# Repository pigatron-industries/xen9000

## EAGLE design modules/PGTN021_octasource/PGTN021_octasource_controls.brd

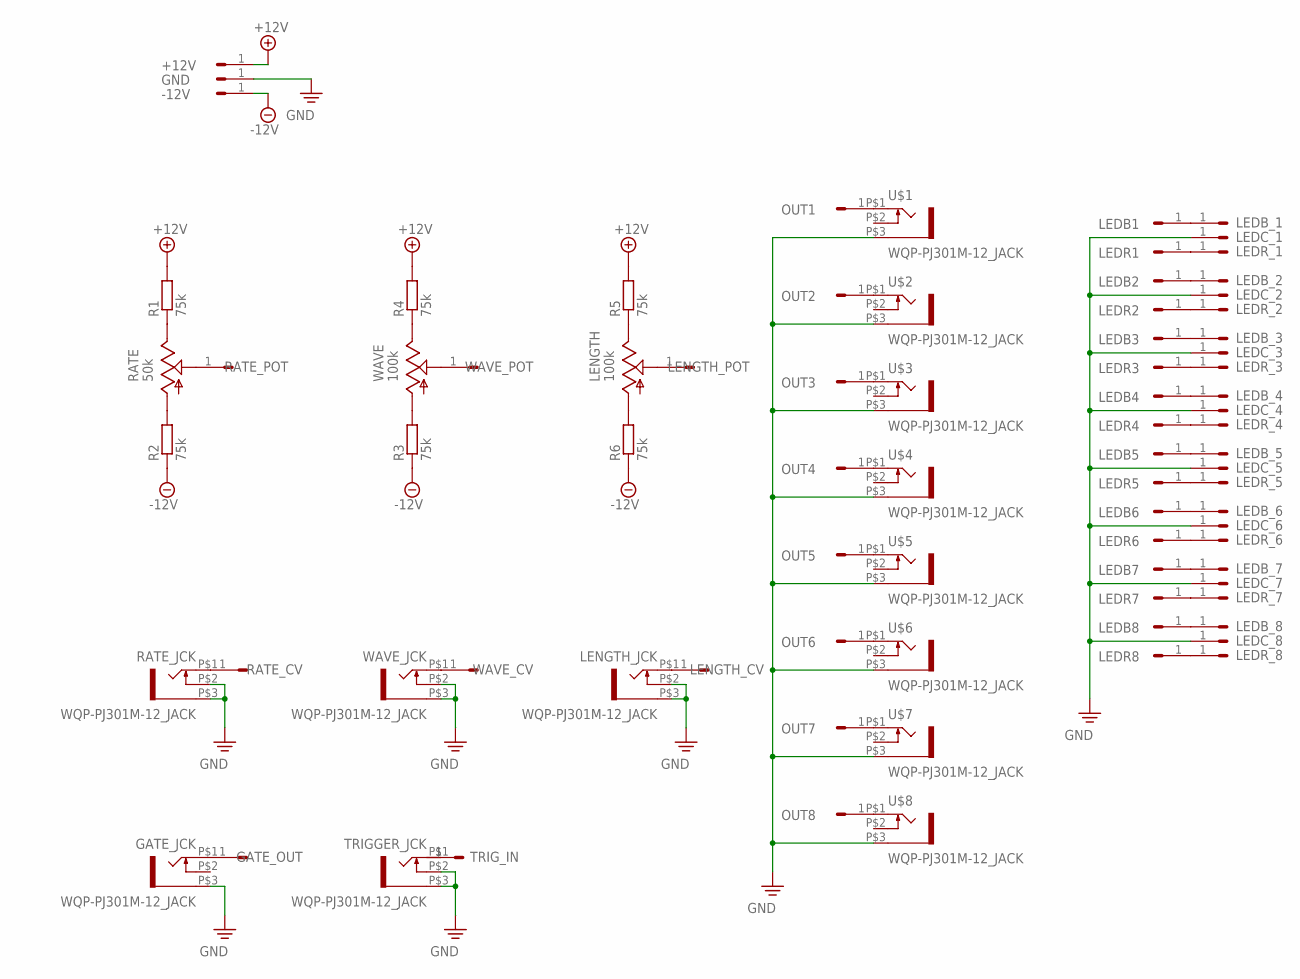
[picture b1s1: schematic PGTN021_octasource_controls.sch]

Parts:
+12V: HEADER/MALE/01
-12V: HEADER/MALE/01
GATE_JCK: WQP-PJ301M-12_JACK
GATE_OUT: HEADER/MALE/01
GND: HEADER/MALE/01
LEDB1, LEDB2, LEDB3, LEDB4, LEDB5, LEDB6, LEDB7, LEDB8: HEADER/MALE/01
LEDB_1, LEDB_2, LEDB_3, LEDB_4, LEDB_5, LEDB_6, LEDB_7, LEDB_8: HEADER/MALE/01
LEDC_1, LEDC_2, LEDC_3, LEDC_4, LEDC_5, LEDC_6, LEDC_7, LEDC_8: HEADER/MALE/01
LEDR1, LEDR2, LEDR3, LEDR4, LEDR5, LEDR6, LEDR7, LEDR8: HEADER/MALE/01
LEDR_1, LEDR_2, LEDR_3, LEDR_4, LEDR_5, LEDR_6, LEDR_7, LEDR_8: HEADER/MALE/01
LENGTH: 100k; 9MM_SNAP-IN_POT
LENGTH_CV: HEADER/MALE/01
LENGTH_JCK: WQP-PJ301M-12_JACK
LENGTH_POT: HEADER/MALE/01
OUT1, OUT2, OUT3, OUT4, OUT5, OUT6, OUT7, OUT8: HEADER/MALE/01
R1, R2, R3, R4, R5, R6: 75k; RESISTOR/7.5
RATE: 50k; 9MM_SNAP-IN_POT
RATE_CV: HEADER/MALE/01
RATE_JCK: WQP-PJ301M-12_JACK
RATE_POT: HEADER/MALE/01
TRIGGER_JCK: WQP-PJ301M-12_JACK
TRIG_IN: HEADER/MALE/01
U$1, U$2, U$3, U$4, U$5, U$6, U$7, U$8: WQP-PJ301M-12_JACK
WAVE: 100k; 9MM_SNAP-IN_POT
WAVE_CV: HEADER/MALE/01
WAVE_JCK: WQP-PJ301M-12_JACK
WAVE_POT: HEADER/MALE/01

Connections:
+12V: +12V.1, R1.2, R4.2, R5.2
-12V: -12V.1, R2.1, R3.1, R6.1
unnamed: R2.2, RATE.1 (A)
unnamed: R1.1, RATE.3 (E)
unnamed: RATE_CV.1, RATE_JCK.P$1 (2)
unnamed: RATE.2 (S), RATE_POT.1
unnamed: R3.2, WAVE.1 (A)
unnamed: R4.1, WAVE.3 (E)
unnamed: WAVE.2 (S), WAVE_POT.1
unnamed: LENGTH.3 (E), R5.1
unnamed: LENGTH.1 (A), R6.2
unnamed: LENGTH.2 (S), LENGTH_POT.1
unnamed: LENGTH_CV.1, LENGTH_JCK.P$1 (2)
unnamed: WAVE_CV.1, WAVE_JCK.P$1 (2)
unnamed: GATE_JCK.P$1 (2), GATE_OUT.1
unnamed: OUT1.1, U$1.P$1 (2)
unnamed: OUT2.1, U$2.P$1 (2)
unnamed: OUT3.1, U$3.P$1 (2)
unnamed: OUT4.1, U$4.P$1 (2)
unnamed: OUT5.1, U$5.P$1 (2)
unnamed: OUT6.1, U$6.P$1 (2)
unnamed: OUT7.1, U$7.P$1 (2)
unnamed: OUT8.1, U$8.P$1 (2)
unnamed: LEDB1.1, LEDB_1.1
unnamed: LEDB2.1, LEDB_2.1
unnamed: LEDB3.1, LEDB_3.1
unnamed: LEDB4.1, LEDB_4.1
unnamed: LEDB5.1, LEDB_5.1
unnamed: LEDB6.1, LEDB_6.1
unnamed: LEDB7.1, LEDB_7.1
unnamed: LEDB8.1, LEDB_8.1
unnamed: LEDR1.1, LEDR_1.1
unnamed: LEDR2.1, LEDR_2.1
unnamed: LEDR3.1, LEDR_3.1
unnamed: LEDR4.1, LEDR_4.1
unnamed: LEDR5.1, LEDR_5.1
unnamed: LEDR6.1, LEDR_6.1
unnamed: LEDR7.1, LEDR_7.1
unnamed: LEDR8.1, LEDR_8.1
unnamed: TRIGGER_JCK.P$1 (2), TRIG_IN.1
PE: GATE_JCK.P$3 (1), GND.1, LEDC_1.1, LEDC_2.1, LEDC_3.1, LEDC_4.1, LEDC_5.1, LEDC_6.1, LEDC_7.1, LEDC_8.1, LENGTH_JCK.P$2 (3), LENGTH_JCK.P$3 (1), RATE_JCK.P$2 (3), RATE_JCK.P$3 (1), TRIGGER_JCK.P$2 (3), TRIGGER_JCK.P$3 (1), U$1.P$3 (1), U$2.P$3 (1), U$3.P$3 (1), U$4.P$3 (1), U$5.P$3 (1), U$6.P$3 (1), U$7.P$3 (1), U$8.P$3 (1), WAVE_JCK.P$2 (3), WAVE_JCK.P$3 (1)

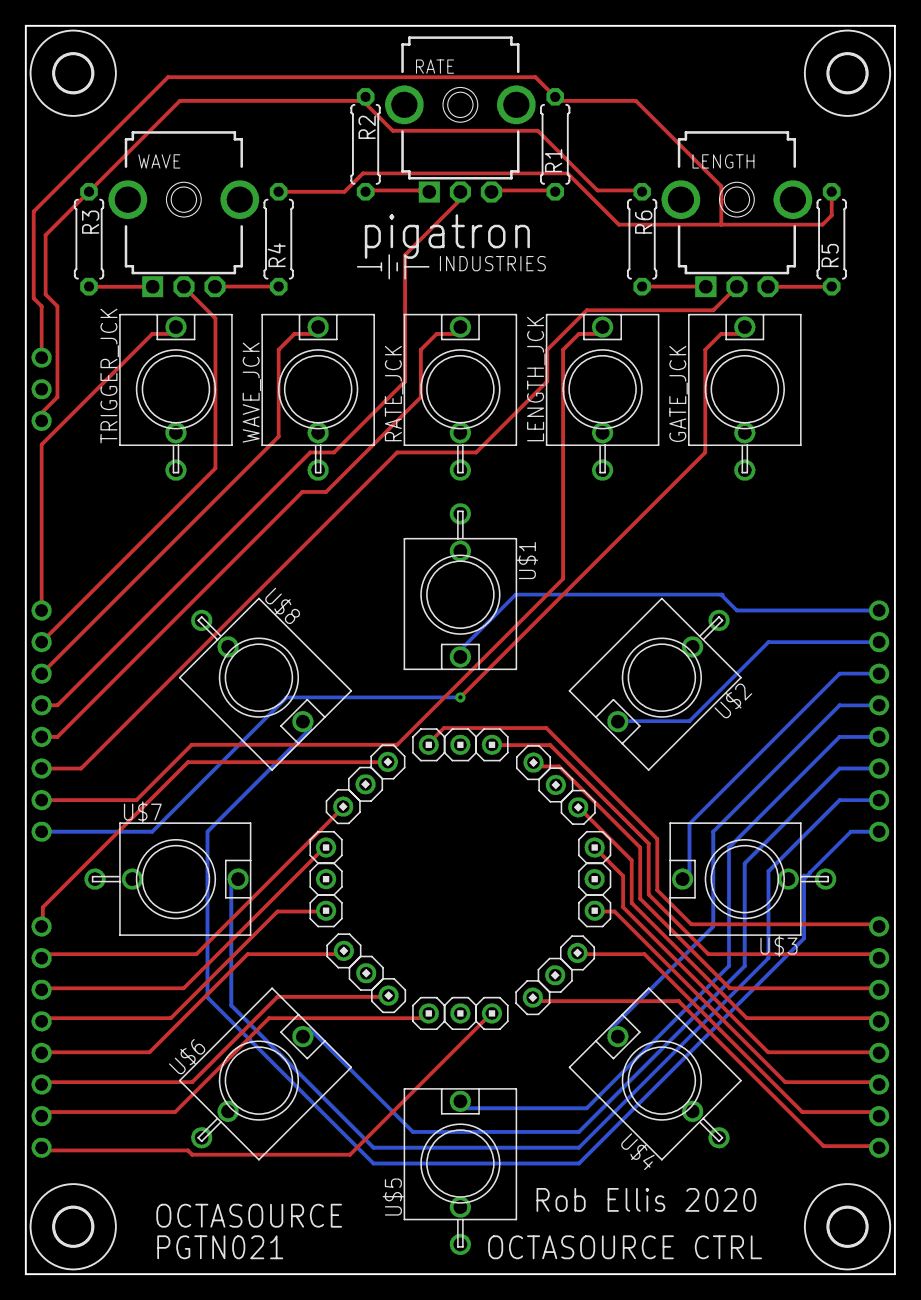
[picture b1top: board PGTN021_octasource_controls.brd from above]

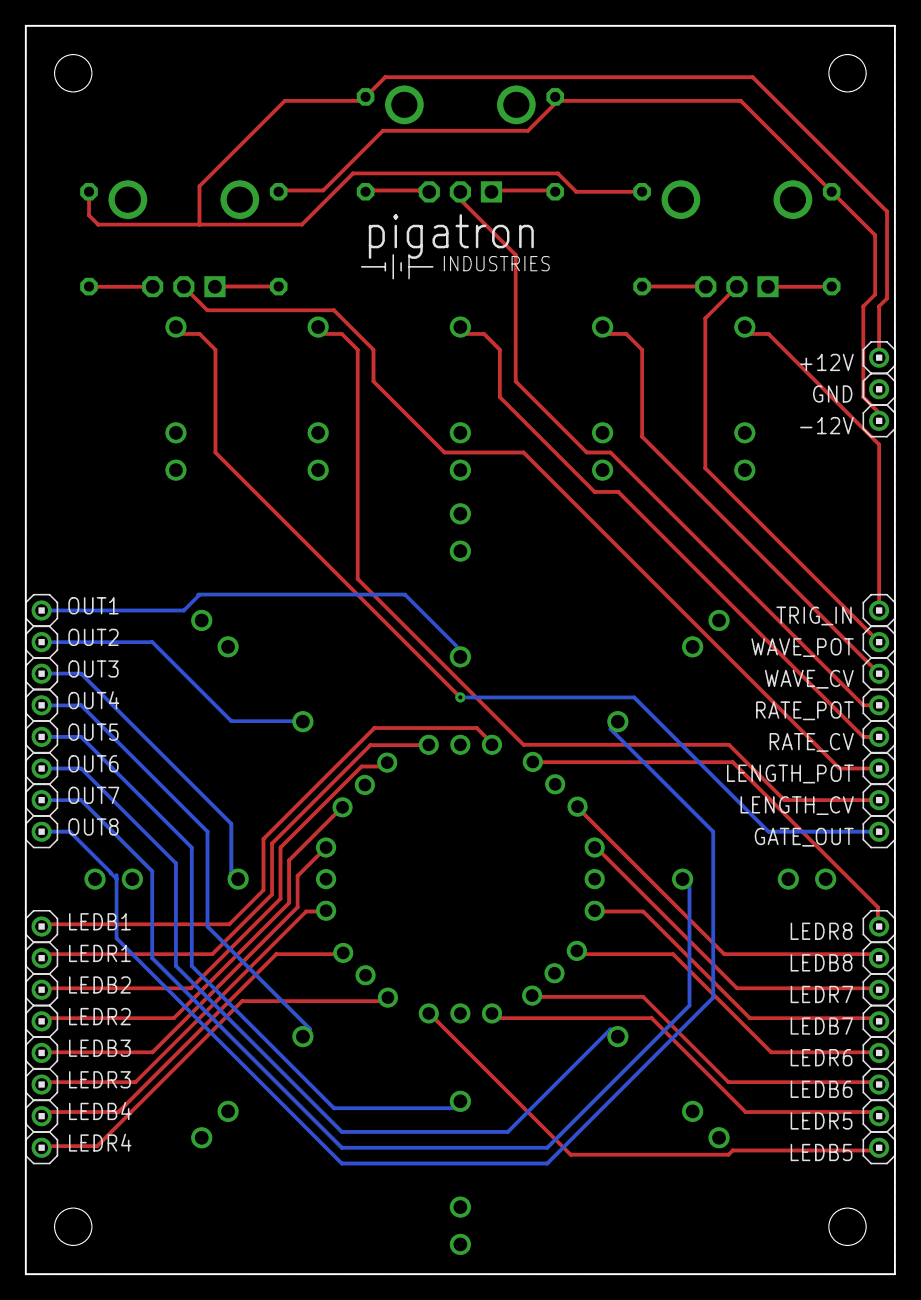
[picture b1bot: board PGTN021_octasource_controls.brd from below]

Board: 2 copper layers, 69.8 x 100.3 mm, 87 parts (36 on the bottom side), 41 nets.

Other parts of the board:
U$9, U$10, U$11, U$12: STANDOFF/3.0
U$13, U$14: PIGATRON-LOGO

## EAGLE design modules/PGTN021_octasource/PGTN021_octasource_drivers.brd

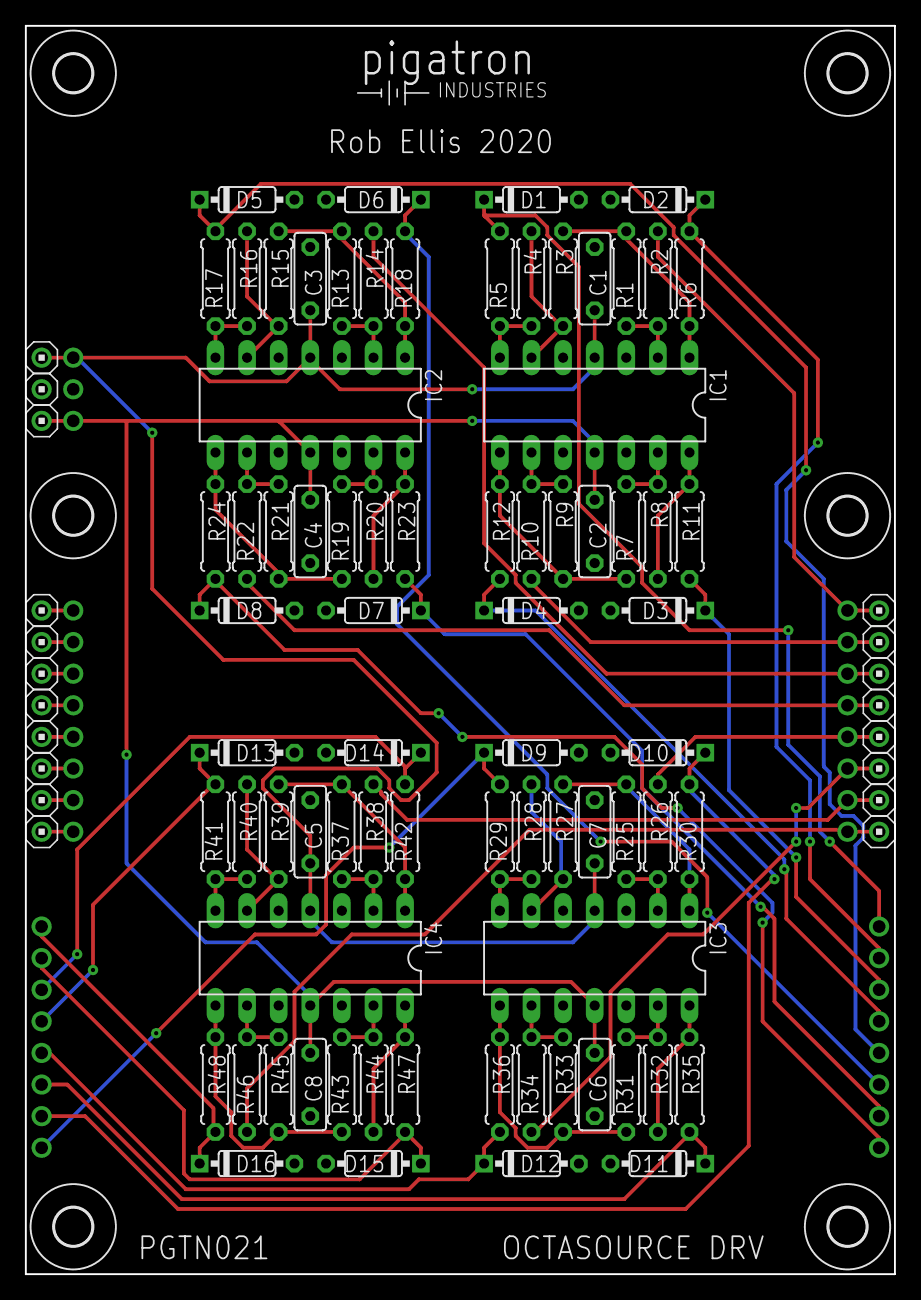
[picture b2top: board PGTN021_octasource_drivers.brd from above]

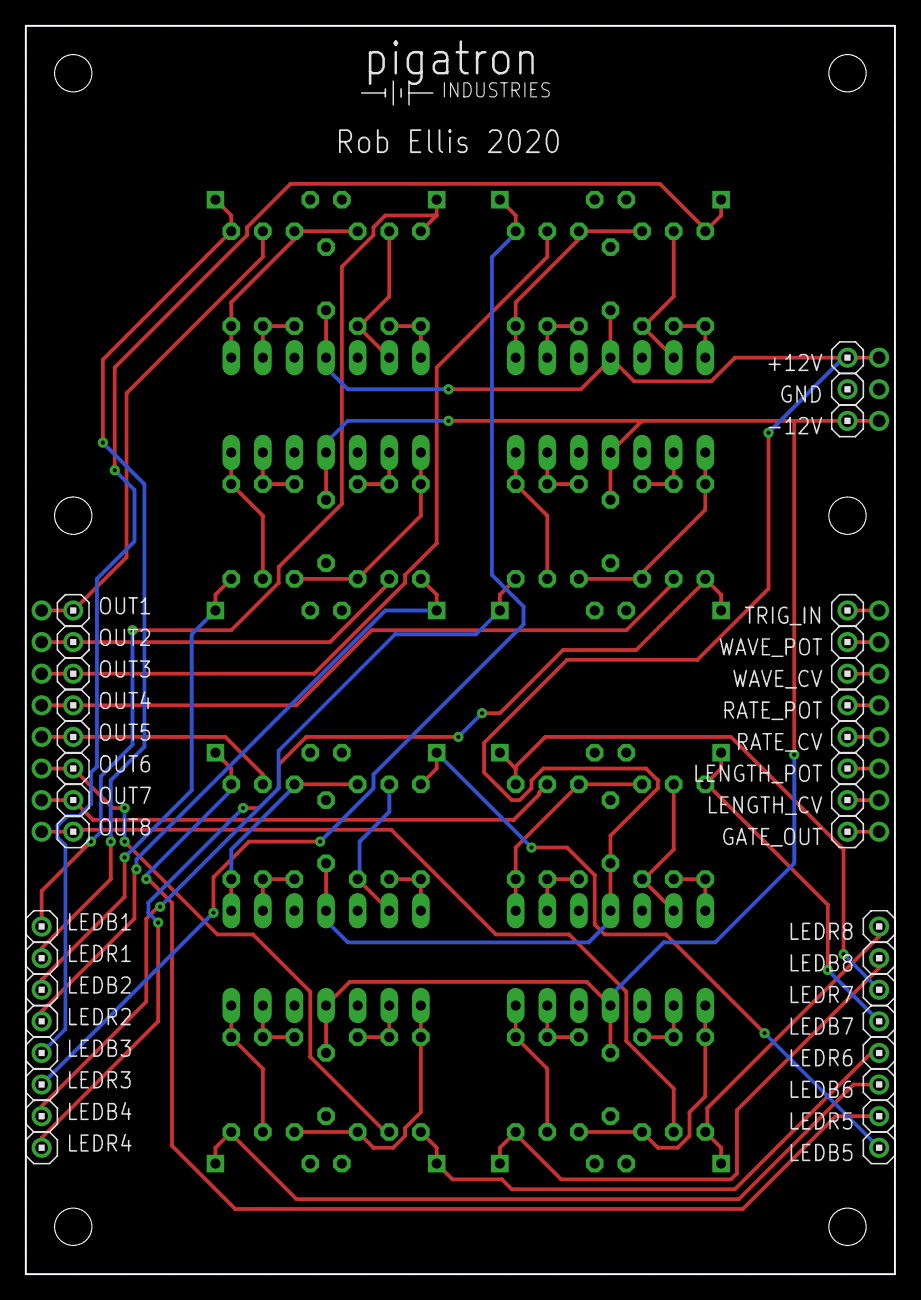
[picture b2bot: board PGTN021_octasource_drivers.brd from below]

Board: 2 copper layers, 69.8 x 100.3 mm, 138 parts (36 on the bottom side), 67 nets.

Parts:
+12V, +12V1: HEADER/MALE/01
-12V, -12V1: HEADER/MALE/01
C1, C2, C3, C4, C5, C6, C7, C8: CERAMICDISC/5
D1, D2, D3, D4, D5, D6, D7, D8, D9, D10, D11, D12, D13, D14, D15, D16: DO35-7
GATE_OUT, GATE_OUT1: HEADER/MALE/01
GND, GND1: HEADER/MALE/01
IC1, IC2, IC3, IC4: TL084P; DIL14
LEDB1, LEDB2, LEDB3, LEDB4, LEDB5, LEDB6, LEDB7, LEDB8: HEADER/MALE/01
LEDR1, LEDR2, LEDR3, LEDR4, LEDR5, LEDR6, LEDR7, LEDR8: HEADER/MALE/01
LENGTH_CV, LENGTH_CV1: HEADER/MALE/01
LENGTH_POT, LENGTH_POT1: HEADER/MALE/01
OUT1, OUT2, OUT3, OUT4, OUT5, OUT6, OUT7, OUT8, OUT9, OUT10, OUT11, OUT12, OUT13, OUT14, OUT15, OUT16: HEADER/MALE/01
R1, R9, R13, R21, R25, R33, R37, R45: 100k; RESISTOR/7.5
R2, R3, R4, R7, R8, R10, R14, R15, R16, R19, R20, R22, R26, R27, R28, R31, R32, R34, R38, R39, R40, R43, R44, R46: 10k; RESISTOR/7.5
R5, R11, R17, R23, R29, R35, R41, R47: 2.7k; RESISTOR/7.5
R6, R12, R18, R24, R30, R36, R42, R48: 4.7k; RESISTOR/7.5
RATE_CV, RATE_CV1: HEADER/MALE/01
RATE_POT, RATE_POT1: HEADER/MALE/01
TRIG_IN, TRIG_IN1: HEADER/MALE/01
U$1, U$2: PIGATRON-LOGO
U$4, U$5, U$9, U$10, U$11, U$12: STANDOFF/3.0
WAVE_CV, WAVE_CV1: HEADER/MALE/01
WAVE_POT, WAVE_POT1: HEADER/MALE/01

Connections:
+12V: +12V.1, +12V1.1, C1.1, C3.1, C5.1, C7.1, IC1.4, IC2.4, IC3.4, IC4.4
-12V: -12V.1, -12V1.1, C2.2, C4.2, C6.2, C8.2, IC1.11, IC2.11, IC3.11, IC4.11
unnamed: IC1.6, R3.2, R4.1
unnamed: IC1.2, R1.1, R2.2
unnamed: IC1.1, R1.2, R3.1, R6.1
unnamed: OUT1.1, OUT9.1, R2.1
unnamed: IC1.7, R4.2, R5.1
unnamed: D1.C, LEDB1.1, R5.2
unnamed: D2.C, LEDR1.1, R6.2
unnamed: IC1.13, R7.2, R8.1
unnamed: IC1.9, R9.1, R10.2
unnamed: OUT2.1, OUT10.1, R10.1
unnamed: IC1.14, R8.2, R11.1
unnamed: IC1.8, R7.1, R9.2, R12.1
unnamed: IC2.2, R13.1, R14.2
unnamed: D3.C, LEDB2.1, R11.2
unnamed: D4.C, LEDR2.1, R12.2
unnamed: IC2.1, R13.2, R15.1, R18.1
unnamed: IC2.6, R15.2, R16.1
unnamed: OUT3.1, OUT11.1, R14.1
unnamed: IC2.7, R16.2, R17.1
unnamed: D5.C, LEDB3.1, R17.2
unnamed: D6.C, LEDR3.1, R18.2
unnamed: IC2.13, R19.2, R20.1
unnamed: IC2.9, R21.1, R22.2
unnamed: IC2.14, R20.2, R23.1
unnamed: IC2.8, R19.1, R21.2, R24.1
unnamed: D7.C, LEDB4.1, R23.2
unnamed: D8.C, LEDR4.1, R24.2
unnamed: OUT4.1, OUT12.1, R22.1
unnamed: IC3.2, R25.1, R26.2
unnamed: IC3.1, R25.2, R27.1, R30.1
unnamed: IC3.6, R27.2, R28.1
unnamed: OUT5.1, OUT13.1, R26.1
unnamed: IC3.7, R28.2, R29.1
unnamed: D9.C, LEDB5.1, R29.2
unnamed: D10.C, LEDR5.1, R30.2
unnamed: IC3.13, R31.2, R32.1
unnamed: IC3.9, R33.1, R34.2
unnamed: IC3.14, R32.2, R35.1
unnamed: IC3.8, R31.1, R33.2, R36.1
unnamed: D11.C, LEDB6.1, R35.2
unnamed: D12.C, LEDR6.1, R36.2
unnamed: OUT6.1, OUT14.1, R34.1
unnamed: RATE_POT.1, RATE_POT1.1
unnamed: IC4.2, R37.1, R38.2
unnamed: IC4.1, R37.2, R39.1, R42.1
unnamed: IC4.6, R39.2, R40.1
unnamed: OUT7.1, OUT15.1, R38.1
unnamed: IC4.7, R40.2, R41.1
unnamed: D13.C, LEDB7.1, R41.2
unnamed: D14.C, LEDR7.1, R42.2
unnamed: IC4.13, R43.2, R44.1
unnamed: IC4.9, R45.1, R46.2
unnamed: IC4.14, R44.2, R47.1
unnamed: IC4.8, R43.1, R45.2, R48.1
unnamed: D15.C, LEDB8.1, R47.2
unnamed: D16.C, LEDR8.1, R48.2
unnamed: OUT8.1, OUT16.1, R46.1
unnamed: RATE_CV.1, RATE_CV1.1
unnamed: GATE_OUT.1, GATE_OUT1.1
unnamed: TRIG_IN.1, TRIG_IN1.1
unnamed: WAVE_CV.1, WAVE_CV1.1
unnamed: LENGTH_CV.1, LENGTH_CV1.1
unnamed: LENGTH_POT.1, LENGTH_POT1.1
unnamed: WAVE_POT.1, WAVE_POT1.1
PE: C1.2, C2.1, C3.2, C4.1, C5.2, C6.1, C7.2, C8.1, D1.A, D2.A, D3.A, D4.A, D5.A, D6.A, D7.A, D8.A, D9.A, D10.A, D11.A, D12.A, D13.A, D14.A, D15.A, D16.A, GND.1, GND1.1, IC1.3, IC1.5, IC1.10, IC1.12, IC2.3, IC2.5, IC2.10, IC2.12, IC3.3, IC3.5, IC3.10, IC3.12, IC4.3, IC4.5, IC4.10, IC4.12

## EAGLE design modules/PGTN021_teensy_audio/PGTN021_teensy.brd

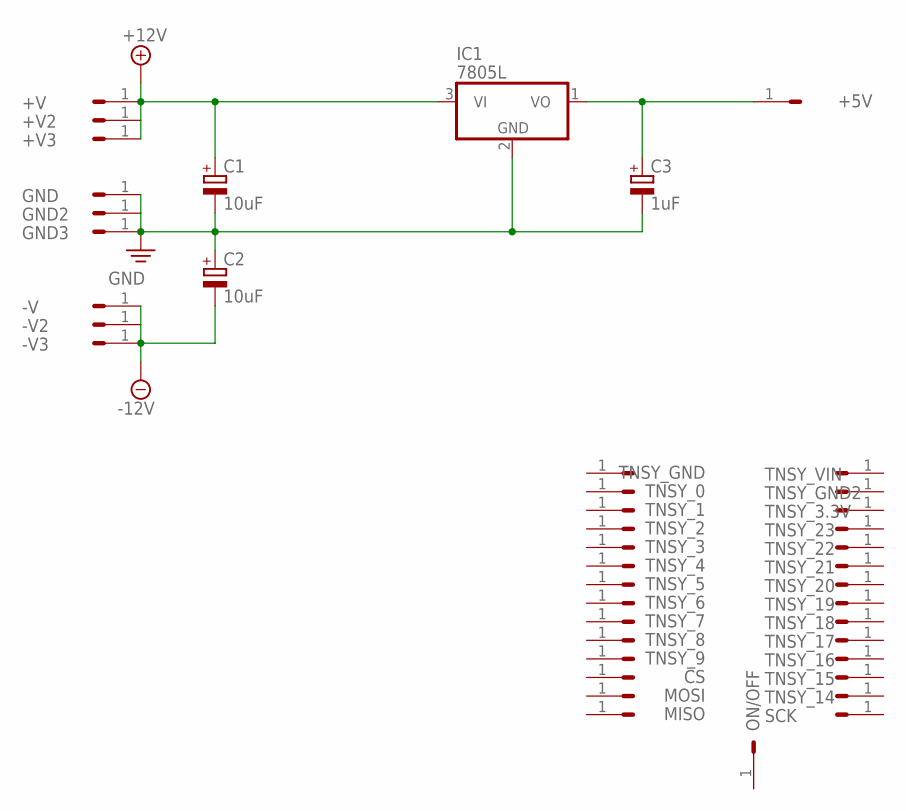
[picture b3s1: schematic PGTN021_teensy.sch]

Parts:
+5V: HEADER/MALE/01
+V, +V2, +V3: HEADER/MALE/01
-V, -V2, -V3: HEADER/MALE/01
C1, C2: 10uF; E2,5-6
C3: 1uF; E2,5-6
CS: HEADER/MALE/01
GND, GND2, GND3: HEADER/MALE/01
IC1: 7805L; TO92
MISO: HEADER/MALE/01
MOSI: HEADER/MALE/01
ON/OFF: HEADER/MALE/01
SCK: HEADER/MALE/01
TNSY_0, TNSY_1, TNSY_2, TNSY_3, TNSY_3.3V, TNSY_4, TNSY_5, TNSY_6, TNSY_7, TNSY_8, TNSY_9, TNSY_14, TNSY_15, TNSY_16, TNSY_17, TNSY_18, TNSY_19, TNSY_20, TNSY_21, TNSY_22, TNSY_23: HEADER/MALE/01
TNSY_GND, TNSY_GND2: HEADER/MALE/01
TNSY_VIN: HEADER/MALE/01

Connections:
+12V: +V.1, +V2.1, +V3.1, C1.+, IC1.3 (VI)
-12V: -V.1, -V2.1, -V3.1, C2.-
GND: C1.-, C2.+, C3.-, GND.1, GND2.1, GND3.1, IC1.2 (GND)
unnamed: +5V.1, C3.+, IC1.1 (VO)

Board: 2 copper layers, 43 parts (0 on the bottom side), 4 nets, no tracks yet.

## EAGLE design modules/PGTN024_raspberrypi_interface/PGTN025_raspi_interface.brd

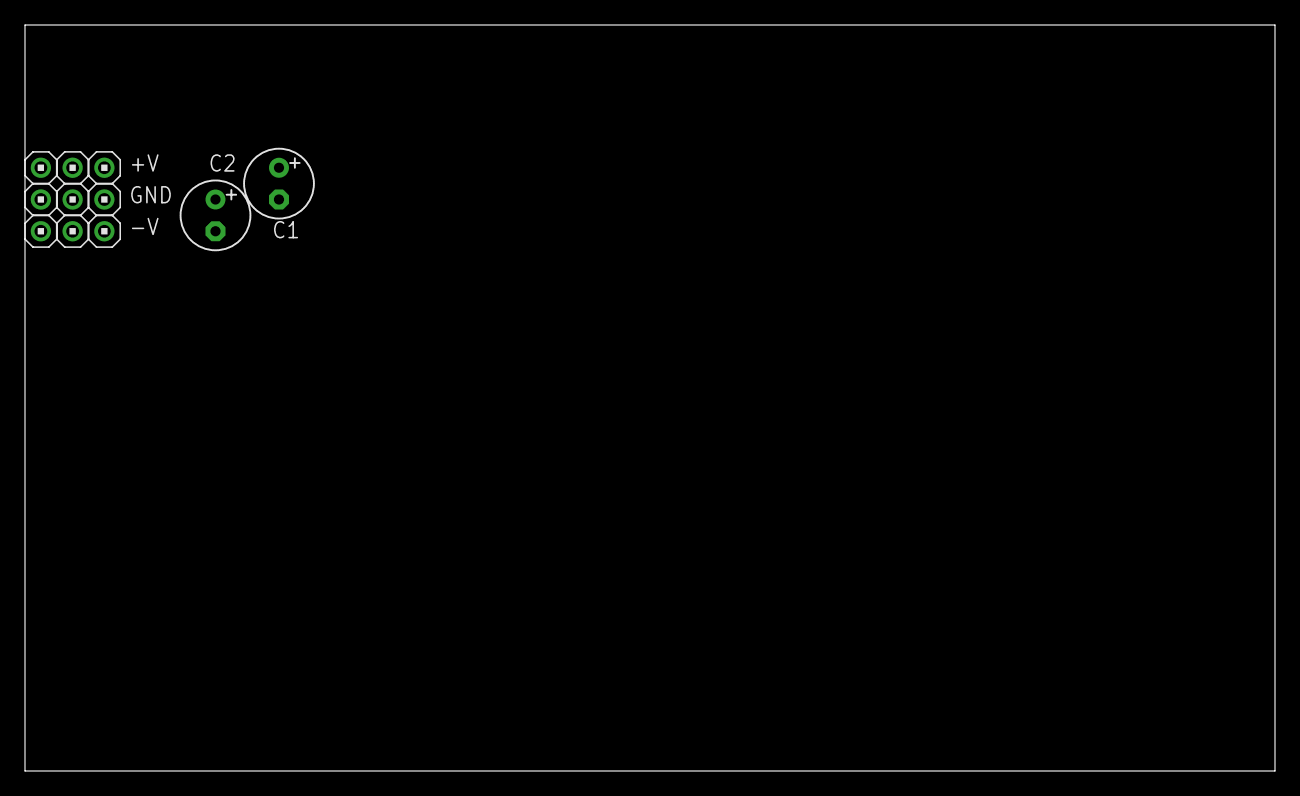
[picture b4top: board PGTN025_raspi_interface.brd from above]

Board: 2 copper layers, 100.0 x 59.7 mm, 11 parts (0 on the bottom side), 3 nets, no tracks yet.

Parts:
+V, +V2, +V3: HEADER/MALE/01
-V, -V2, -V3: HEADER/MALE/01
C1, C2: 10uF; E2,5-6
GND, GND2, GND3: HEADER/MALE/01

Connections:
+12V: +V.1, +V2.1, +V3.1, C1.+
-12V: -V.1, -V2.1, -V3.1, C2.-
GND: C1.-, C2.+, GND.1, GND2.1, GND3.1

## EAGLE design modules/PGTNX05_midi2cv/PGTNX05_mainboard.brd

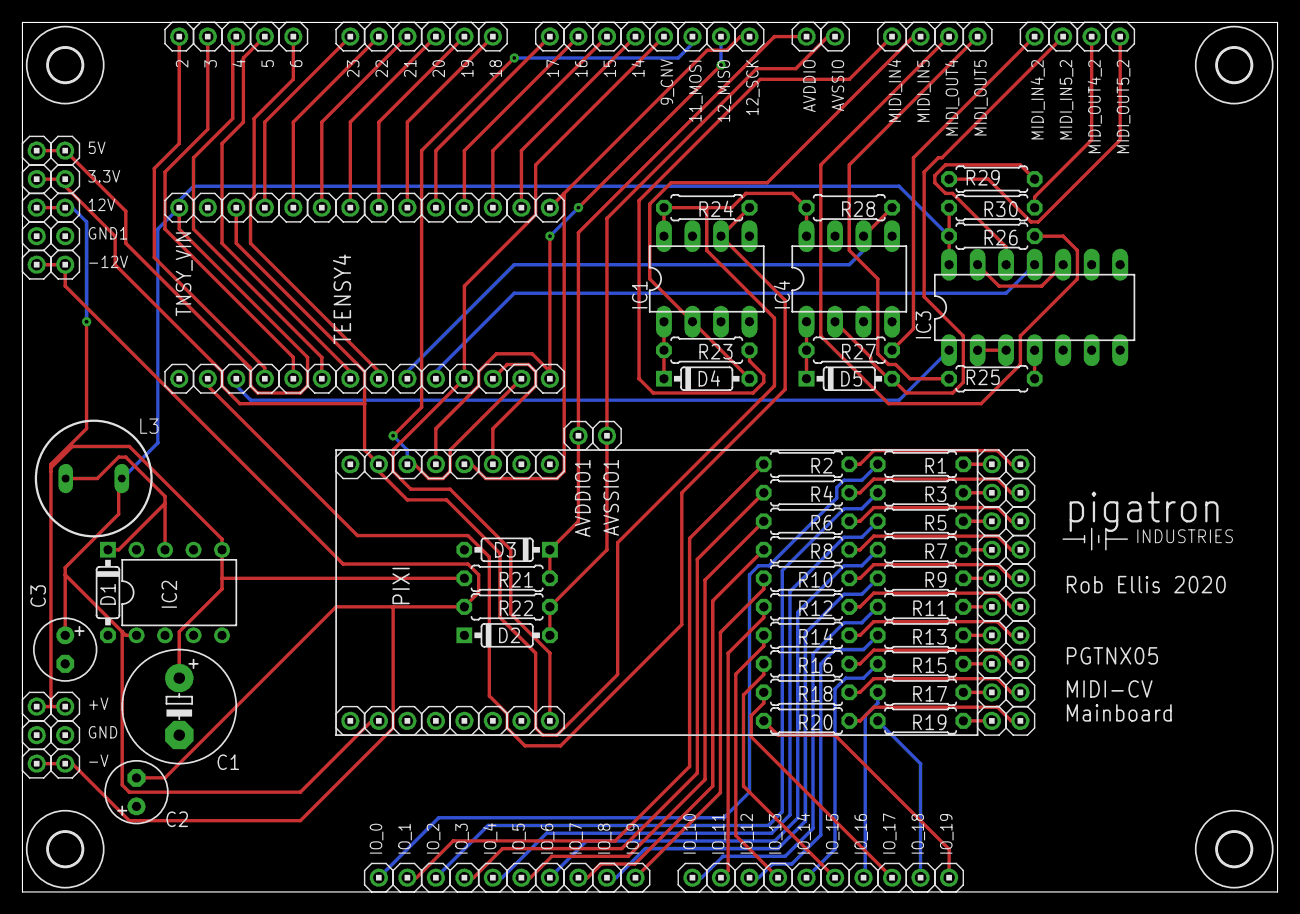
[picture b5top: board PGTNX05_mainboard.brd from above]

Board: 2 copper layers, 111.8 x 77.5 mm, 179 parts (0 on the bottom side), 86 nets.

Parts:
2, 3, 3.3V, 3.3V1, 4, 5, 5V, 5V1, 6, 9_CNV, 11_MOSI, 12V, 12_MISO, 12_SCK, 14, 15, 16, 17, 18, 19, 20, 21, 22, 23: HEADER/MALE/01
+V, +V2, +V3: HEADER/MALE/01
-12V: HEADER/MALE/01
-V, -V1, -V2: HEADER/MALE/01
AVDDIO, AVDDIO1: HEADER/MALE/01
AVSSIO, AVSSIO1: HEADER/MALE/01
C1: 22uF; E5-10,5
C2: 10uF; E2,5-6
C3: 220uF; E2,5-6
D1: 1N5819; DO35-7
D2, D3, D4, D5: DO35-7
GND, GND1, GND2, GND3: HEADER/MALE/01
IC1, IC4: H11L1; DIL08
IC2: LM2574N-5.0; DIL08
IC3: 40106N; DIL14
IO_0, IO_1, IO_2, IO_3, IO_4, IO_5, IO_6, IO_7, IO_8, IO_9, IO_10, IO_11, IO_12, IO_13, IO_14, IO_15, IO_16, IO_17, IO_18, IO_19: HEADER/MALE/01
L3: 330uH; BS11
MIDI_IN4, MIDI_IN4_2, MIDI_IN5, MIDI_IN5_2: HEADER/MALE/01
MIDI_OUT4, MIDI_OUT4_2, MIDI_OUT5, MIDI_OUT5_2: HEADER/MALE/01
PIXI_0, PIXI_1, PIXI_2, PIXI_3, PIXI_3.3V, PIXI_4, PIXI_5, PIXI_5V, PIXI_6, PIXI_7, PIXI_8, PIXI_9, PIXI_10, PIXI_11, PIXI_12, PIXI_13, PIXI_14, PIXI_15, PIXI_16, PIXI_17, PIXI_18, PIXI_19: HEADER/MALE/01
PIXI_CNV: HEADER/MALE/01
PIXI_CS: HEADER/MALE/01
PIXI_GND, PIXI_GND2: HEADER/MALE/01
PIXI_INT: HEADER/MALE/01
PIXI_NC1, PIXI_NC2, PIXI_NC3, PIXI_NC4, PIXI_NC5, PIXI_NC6: HEADER/MALE/01
PIXI_SCK: HEADER/MALE/01
PIXI_SDI: HEADER/MALE/01
PIXI_SDO: HEADER/MALE/01
R1, R2, R3, R4, R5, R6, R7, R8, R9, R10, R11, R12, R13, R14, R15, R16, R17, R18, R19, R20, R21, R22: RESISTOR/7.5
R23, R24, R25, R26, R27, R28, R29, R30: 220R; RESISTOR/7.5
TNSY_0, TNSY_1, TNSY_2, TNSY_3, TNSY_3.3V, TNSY_4, TNSY_5, TNSY_6, TNSY_7, TNSY_8, TNSY_9, TNSY_14, TNSY_15, TNSY_16, TNSY_17, TNSY_18, TNSY_19, TNSY_20, TNSY_21, TNSY_22, TNSY_23: HEADER/MALE/01
TNSY_CS: HEADER/MALE/01
TNSY_GND, TNSY_GND2: HEADER/MALE/01
TNSY_MISO: HEADER/MALE/01
TNSY_MOSI: HEADER/MALE/01
TNSY_SCK: HEADER/MALE/01
TNSY_VIN: HEADER/MALE/01
U$2, U$3, U$4, U$7: STANDOFF/3.0
U$5: PIGATRON-LOGO

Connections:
3.3V: 3.3V.1, 3.3V1.1, IC1.8, IC4.8, PIXI_3.3V.1, R24.2, R28.2, TNSY_3.3V.1
5V: 5V.1, 5V1.1, C3.+, IC2.1, IC3.14, L3.2, PIXI_5V.1, R26.2, R30.2, TNSY_VIN.1
+12V: 12V.1, +V.1, +V2.1, +V3.1, C1.+, IC2.5, R21.2
-12V: -12V.1, -V.1, -V1.1, -V2.1, C2.-, R22.2
GND: C1.-, C2.+, C3.-, D1.A, D2.C, D3.A, GND.1, GND1.1, GND2.1, GND3.1, IC1.7, IC2.2, IC2.3, IC2.4, IC3.7, IC4.7, PIXI_GND.1, PIXI_GND2.1, TNSY_GND.1
unnamed: 17.1, TNSY_17.1
unnamed: 16.1, TNSY_16.1
unnamed: D1.C, IC2.7, L3.1
unnamed: 12_MISO.1, PIXI_SDO.1, TNSY_MISO.1
unnamed: PIXI_CS.1, TNSY_CS.1
unnamed: 18.1, TNSY_18.1
unnamed: 19.1, TNSY_19.1
unnamed: 20.1, TNSY_20.1
unnamed: 21.1, TNSY_21.1
unnamed: 22.1, TNSY_22.1
unnamed: 23.1, TNSY_23.1
unnamed: 15.1, TNSY_15.1
unnamed: 2.1, TNSY_2.1
unnamed: 3.1, TNSY_3.1
unnamed: 4.1, TNSY_4.1
unnamed: 5.1, TNSY_5.1
unnamed: PIXI_0.1, R1.1
unnamed: IO_0.1, R1.2
unnamed: PIXI_1.1, R2.1
unnamed: 6.1, TNSY_6.1
unnamed: IO_1.1, R2.2
unnamed: 9_CNV.1, PIXI_CNV.1, TNSY_9.1
unnamed: 11_MOSI.1, PIXI_SDI.1, TNSY_MOSI.1
unnamed: PIXI_2.1, R3.1
unnamed: 12_SCK.1, PIXI_SCK.1, TNSY_SCK.1
unnamed: 14.1, TNSY_14.1
unnamed: IO_2.1, R3.2
unnamed: PIXI_3.1, R4.1
unnamed: IO_3.1, R4.2
unnamed: PIXI_4.1, R5.1
unnamed: IO_4.1, R5.2
unnamed: PIXI_5.1, R6.1
unnamed: IO_5.1, R6.2
unnamed: PIXI_6.1, R7.1
unnamed: IO_6.1, R7.2
unnamed: PIXI_7.1, R8.1
unnamed: IO_7.1, R8.2
unnamed: PIXI_8.1, R9.1
unnamed: IO_8.1, R9.2
unnamed: PIXI_9.1, R10.1
unnamed: IO_9.1, R10.2
unnamed: PIXI_10.1, R11.1
unnamed: IO_10.1, R11.2
unnamed: PIXI_11.1, R12.1
unnamed: IO_11.1, R12.2
unnamed: PIXI_12.1, R13.1
unnamed: IO_12.1, R13.2
unnamed: PIXI_13.1, R14.1
unnamed: IO_13.1, R14.2
unnamed: PIXI_14.1, R15.1
unnamed: IO_14.1, R15.2
unnamed: PIXI_15.1, R16.1
unnamed: IO_15.1, R16.2
unnamed: PIXI_16.1, R17.1
unnamed: IO_16.1, R17.2
unnamed: PIXI_17.1, R18.1
unnamed: IO_17.1, R18.2
unnamed: PIXI_18.1, R19.1
unnamed: IO_18.1, R19.2
unnamed: AVDDIO.1, AVDDIO1.1, D3.C, R21.1
unnamed: AVSSIO.1, AVSSIO1.1, D2.A, R22.1
unnamed: PIXI_19.1, R20.1
unnamed: IO_19.1, R20.2
unnamed: MIDI_IN4.1, R23.1
unnamed: D4.C, IC1.1, R23.2
unnamed: D4.A, IC1.2, MIDI_IN5.1
unnamed: IC3.2, IC3.3
unnamed: IC3.4, R25.2
unnamed: MIDI_OUT5.1, R25.1
unnamed: MIDI_OUT4.1, R26.1
unnamed: MIDI_IN4_2.1, R27.1
unnamed: D5.C, IC4.1, R27.2
unnamed: D5.A, IC4.2, MIDI_IN5_2.1
unnamed: IC3.10, IC3.13
unnamed: IC3.12, R29.2
unnamed: MIDI_OUT5_2.1, R29.1
unnamed: MIDI_OUT4_2.1, R30.1
RX1: IC1.6, R24.1, TNSY_0.1
RX2: IC4.6, R28.1, TNSY_7.1
TX1: IC3.1, TNSY_1.1
TX2: IC3.11, TNSY_8.1

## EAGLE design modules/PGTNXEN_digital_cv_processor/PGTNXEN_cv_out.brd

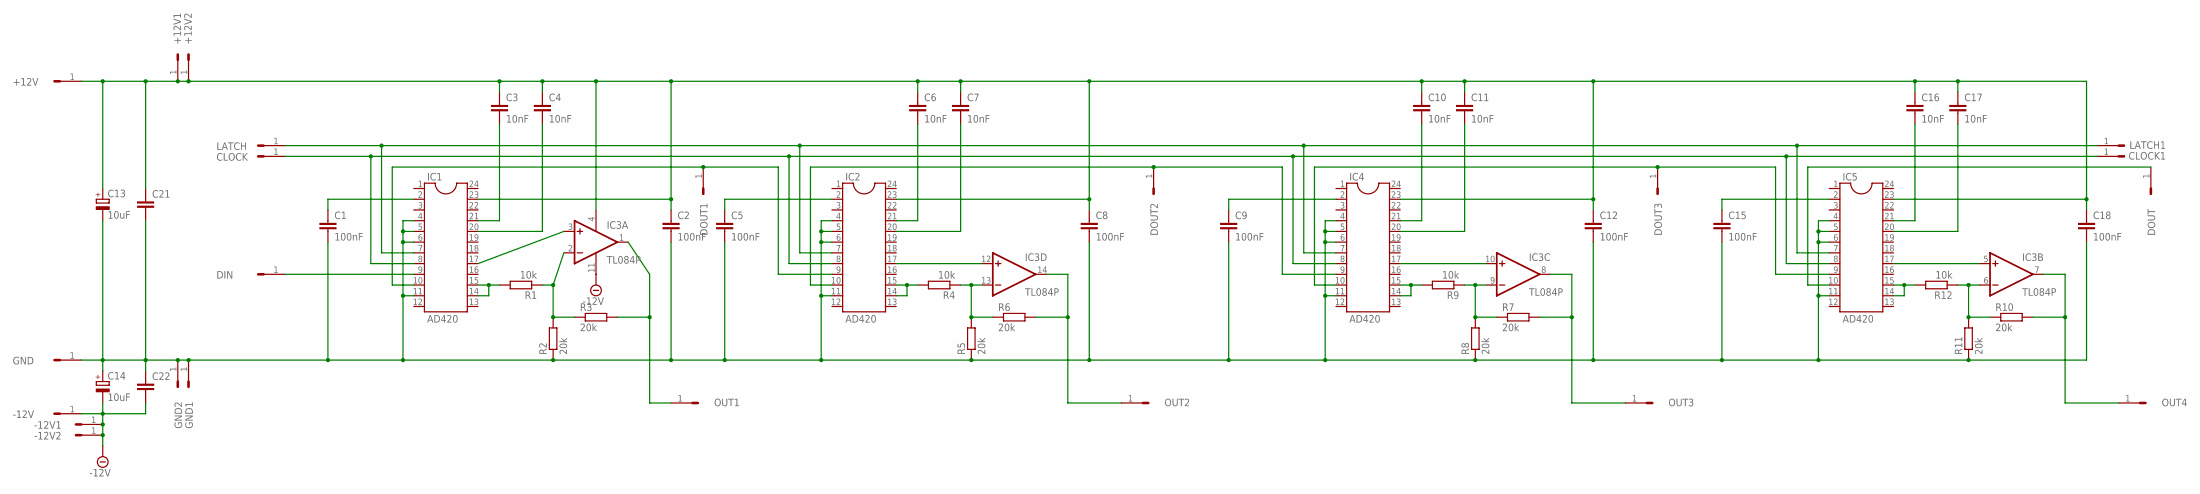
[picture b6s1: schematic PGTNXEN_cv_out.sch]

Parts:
+12V, +12V1, +12V2: HEADER/MALE/01
-12V, -12V1, -12V2: HEADER/MALE/01
C1, C2, C5, C8, C9, C12, C15, C18: 100nF; CERAMICDISC/5
C3, C4, C6, C7, C10, C11, C16, C17: 10nF; CERAMICDISC/5
C13, C14: 10uF; E2,5-6
C21, C22: CAPACITORCERAMICDISC/5; CERAMICDISC/5
CLOCK, CLOCK1: HEADER/MALE/01
DIN: HEADER/MALE/01
DOUT, DOUT1, DOUT2, DOUT3: HEADER/MALE/01
GND, GND1, GND2: HEADER/MALE/01
IC1, IC2, IC4, IC5: AD420; DIL24-3
IC3: TL084P; DIL14
LATCH, LATCH1: HEADER/MALE/01
OUT1, OUT2, OUT3, OUT4: HEADER/MALE/01
R1, R4, R9, R12: 10k; 0204/7
R2, R3, R5, R6, R7, R8, R10, R11: 20k; 0204/7

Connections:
-12V: -12V.1, -12V1.1, -12V2.1, C14.-, C22.2, IC3.11 (V-)
GND: C1.2, C2.2, C5.2, C8.2, C9.2, C12.2, C13.-, C14.+, C15.2, C18.2, C21.2, C22.1, GND.1, GND1.1, GND2.1, IC1.4, IC1.5, IC1.6, IC1.11, IC2.4, IC2.5, IC2.6, IC2.11, IC4.4, IC4.5, IC4.6, IC4.11, IC5.4, IC5.5, IC5.6, IC5.11, R2.1, R5.1, R8.1, R11.1
unnamed: CLOCK.1, CLOCK1.1, IC1.8, IC2.8, IC4.8, IC5.8
unnamed: IC2.17, IC3.12 (+IN)
unnamed: DIN.1, IC1.9
unnamed: IC2.14, IC2.15, R4.2
unnamed: DOUT.1, IC5.10
unnamed: IC3.2 (-IN), R1.1, R2.2, R3.1
unnamed: +12V.1, +12V1.1, +12V2.1, C2.1, C3.1, C4.1, C6.1, C7.1, C8.1, C10.1, C11.1, C12.1, C13.+, C16.1, C17.1, C18.1, C21.1, IC1.23, IC2.23, IC3.4 (V+), IC4.23, IC5.23
unnamed: C1.1, IC1.2
unnamed: C3.2, IC1.21
unnamed: C4.2, IC1.20
unnamed: IC1.17, IC3.3 (+IN)
unnamed: IC1.14, IC1.15, R1.2
unnamed: IC3.1 (OUT), OUT1.1, R3.2
unnamed: IC3.5 (+IN), IC5.17
unnamed: DOUT1.1, IC1.10, IC2.9
unnamed: IC3.14 (OUT), OUT2.1, R6.2
unnamed: C5.1, IC2.2
unnamed: C6.2, IC2.21
unnamed: C7.2, IC2.20
unnamed: IC3.13 (-IN), R4.1, R5.2, R6.1
unnamed: DOUT3.1, IC4.10, IC5.9
unnamed: DOUT2.1, IC2.10, IC4.9
unnamed: IC4.14, IC4.15, R9.2
unnamed: IC3.10 (+IN), IC4.17
unnamed: IC3.8 (OUT), OUT3.1, R7.2
unnamed: C9.1, IC4.2
unnamed: C10.2, IC4.21
unnamed: C11.2, IC4.20
unnamed: IC5.14, IC5.15, R12.2
unnamed: IC3.9 (-IN), R7.1, R8.2, R9.1
unnamed: IC3.7 (OUT), OUT4.1, R10.2
unnamed: C15.1, IC5.2
unnamed: C16.2, IC5.21
unnamed: C17.2, IC5.20
unnamed: IC1.7, IC2.7, IC4.7, IC5.7, LATCH.1, LATCH1.1
unnamed: IC3.6 (-IN), R10.1, R11.2, R12.1

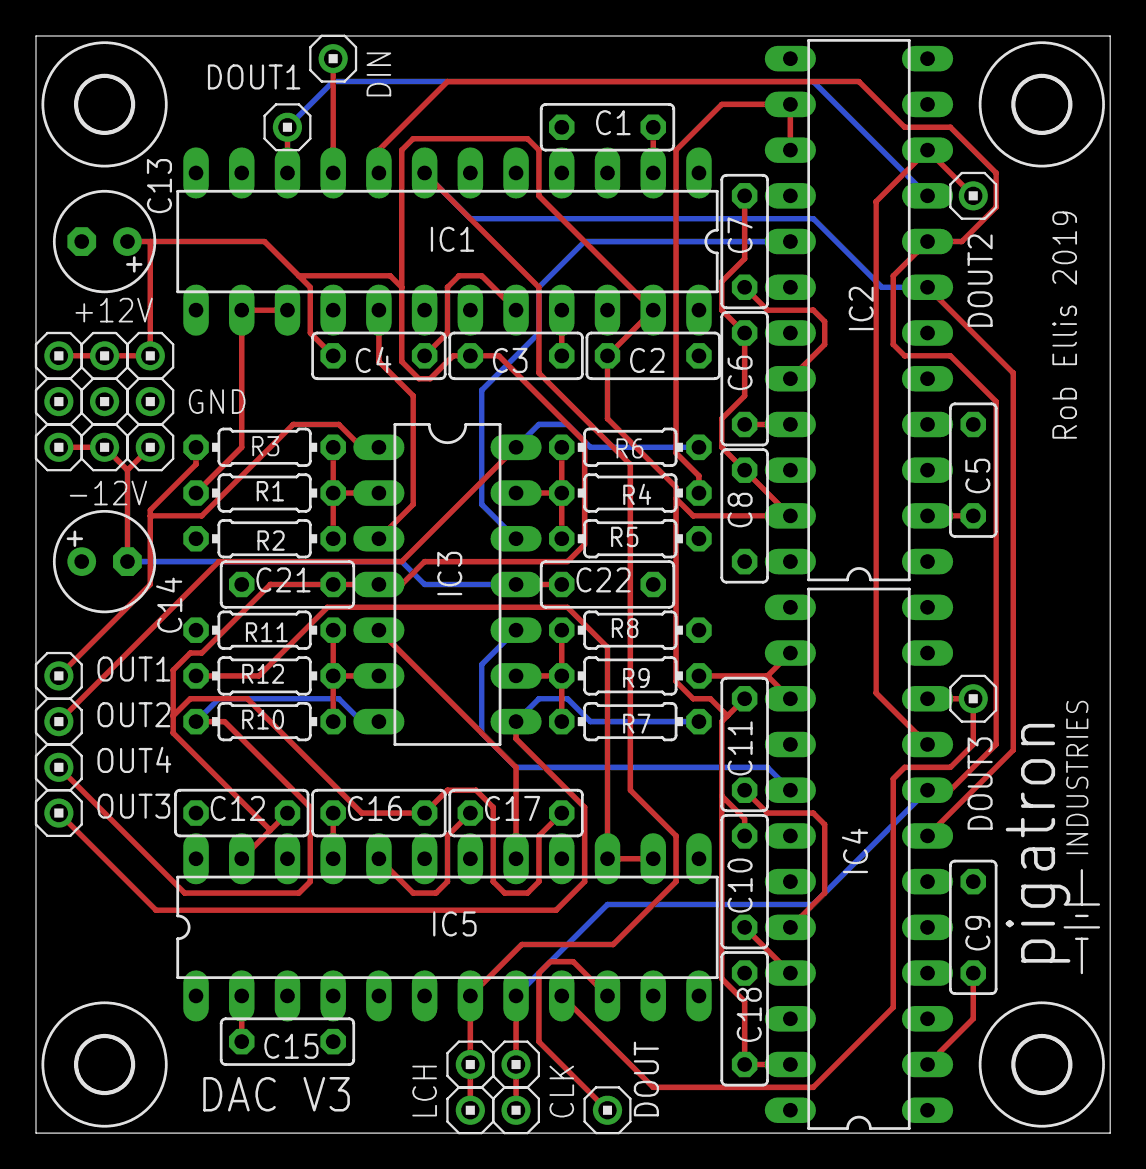
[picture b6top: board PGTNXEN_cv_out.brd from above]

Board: 2 copper layers, 59.7 x 61.0 mm, 64 parts (0 on the bottom side), 38 nets.

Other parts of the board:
U$1, U$2, U$3, U$4: 3,0
U$5: PIGATRON-LOGO

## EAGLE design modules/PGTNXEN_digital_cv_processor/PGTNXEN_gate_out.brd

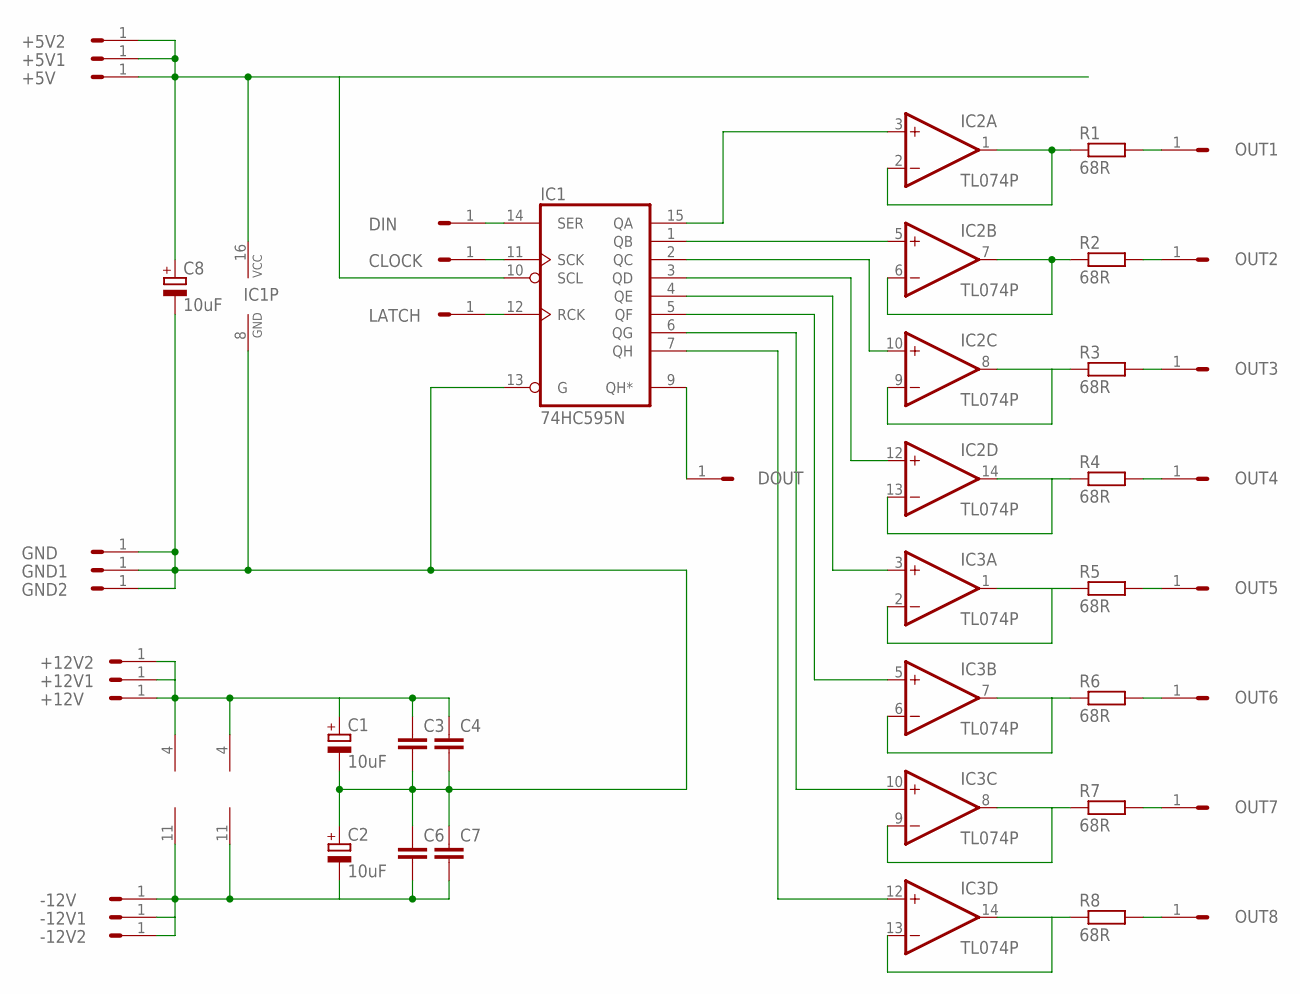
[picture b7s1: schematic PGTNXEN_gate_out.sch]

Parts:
+5V, +5V1, +5V2, +12V, +12V1, +12V2: HEADER/MALE/01
-12V, -12V1, -12V2: HEADER/MALE/01
C1, C2, C8: 10uF; E2,5-6
C3, C4, C6, C7: CAPACITORCERAMICDISC/5; CERAMICDISC/5
CLOCK: HEADER/MALE/01
DIN: HEADER/MALE/01
DOUT: HEADER/MALE/01
GND, GND1, GND2: HEADER/MALE/01
IC1: 74HC595N; DIL16
IC2, IC3: TL074P; DIL14
LATCH: HEADER/MALE/01
OUT1, OUT2, OUT3, OUT4, OUT5, OUT6, OUT7, OUT8: HEADER/MALE/01
R1, R2, R3, R4, R5, R6, R7, R8: 68R; RESISTOR/7.5

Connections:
CLK: +5V.1, +5V1.1, +5V2.1, C8.+, IC1.10 (SCL), IC1.16 (VCC)
GND: C1.-, C2.+, C3.2, C4.2, C6.1, C7.1, C8.-, GND.1, GND1.1, GND2.1, IC1.8 (GND), IC1.13 (G)
unnamed: IC1.15 (QA), IC2.3 (+IN)
unnamed: IC1.1 (QB), IC2.5 (+IN)
unnamed: CLOCK.1, IC1.11 (SCK)
unnamed: DIN.1, IC1.14 (SER)
unnamed: IC1.12 (RCK), LATCH.1
unnamed: IC1.2 (QC), IC2.10 (+IN)
unnamed: IC1.3 (QD), IC2.12 (+IN)
unnamed: IC1.4 (QE), IC3.3 (+IN)
unnamed: IC1.5 (QF), IC3.5 (+IN)
unnamed: IC1.6 (QG), IC3.10 (+IN)
unnamed: IC1.7 (QH), IC3.12 (+IN)
unnamed: DOUT.1, IC1.9 (QH*)
unnamed: IC2.1 (OUT), IC2.2 (-IN), R1.1
unnamed: OUT1.1, R1.2
unnamed: IC2.6 (-IN), IC2.7 (OUT), R2.1
unnamed: OUT2.1, R2.2
unnamed: +12V.1, +12V1.1, +12V2.1, C1.+, C3.1, C4.1, IC2.4 (V+), IC3.4 (V+)
unnamed: -12V.1, -12V1.1, -12V2.1, C2.-, C6.2, C7.2, IC2.11 (V-), IC3.11 (V-)
unnamed: IC2.8 (OUT), IC2.9 (-IN), R3.1
unnamed: IC2.13 (-IN), IC2.14 (OUT), R4.1
unnamed: IC3.1 (OUT), IC3.2 (-IN), R5.1
unnamed: IC3.6 (-IN), IC3.7 (OUT), R6.1
unnamed: IC3.8 (OUT), IC3.9 (-IN), R7.1
unnamed: IC3.13 (-IN), IC3.14 (OUT), R8.1
unnamed: OUT3.1, R3.2
unnamed: OUT4.1, R4.2
unnamed: OUT5.1, R5.2
unnamed: OUT6.1, R6.2
unnamed: OUT7.1, R7.2
unnamed: OUT8.1, R8.2
